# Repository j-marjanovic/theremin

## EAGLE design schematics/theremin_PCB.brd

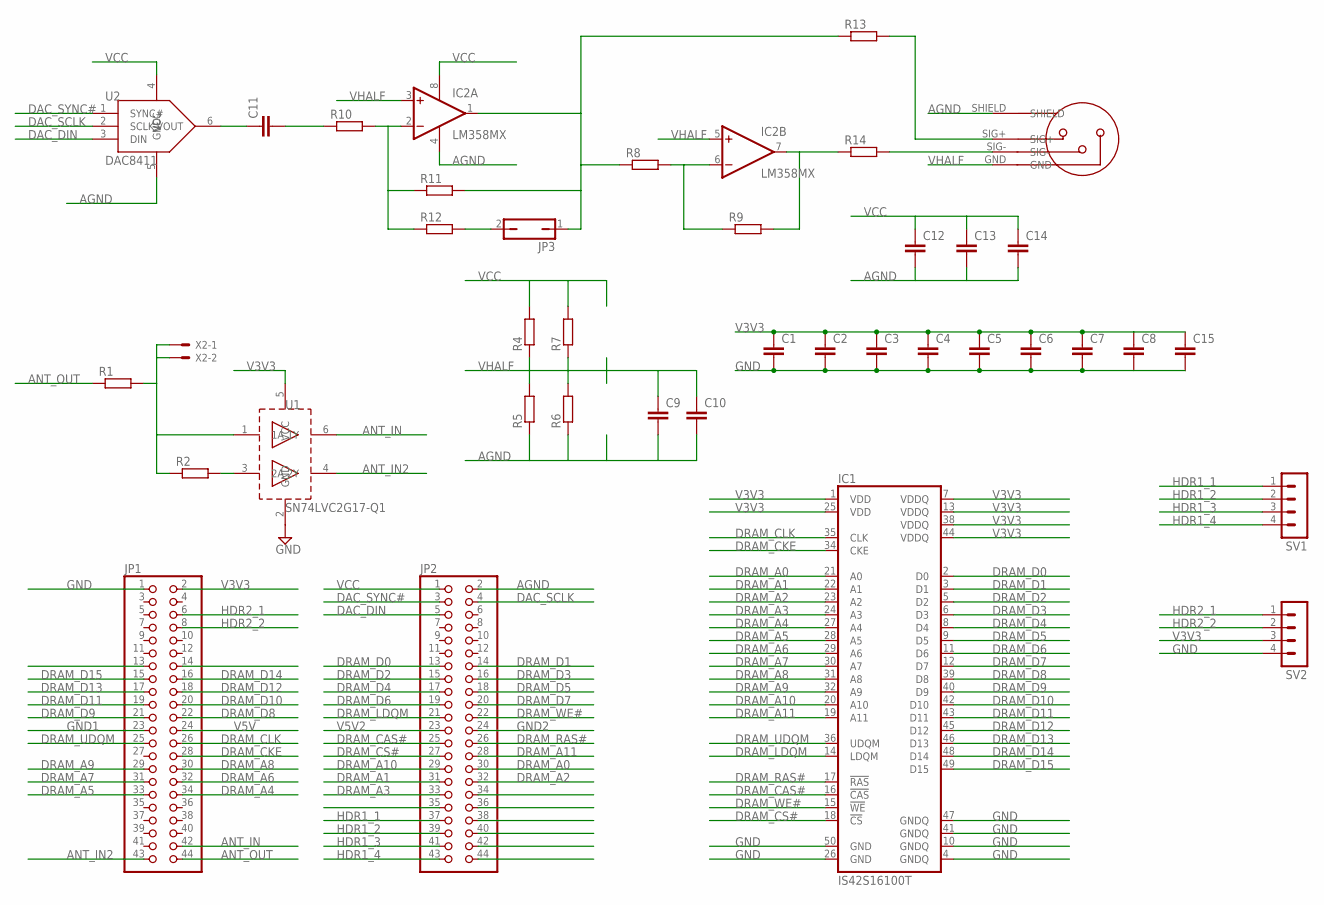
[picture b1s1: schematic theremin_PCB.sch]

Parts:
C1, C2, C3, C4, C5, C6, C7, C8, C9, C10, C11, C12, C13, C14, C15: C-EUC0805; C0805
IC1: IS42S16100T; TSOP50-II
IC2: LM358MX; SO08
JP1, JP2: PINHD-2X22; 2X22
JP3: JP1Q; JP1
R1, R2: R-EU_R0603; R0603
R4, R5, R6, R7, R8, R9, R10, R11, R12, R13, R14: R-EU_M0805; M0805
SV1, SV2: MA04-1
U1: SN74LVC2G17-Q1; DCK_R-PDSO-G6
U2: DAC8411; DCK_R-PDSO-G6
U$1: MINIXLR; MINXLR
X2: KK-156-2

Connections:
AGND: C9.2, C10.2, C12.2, C13.2, C14.2, IC2.4 (V-), JP2.2, R5.1, R6.1, U2.5 (GND), U$1.SHIELD
ANT_IN: JP1.42, U1.6 (1Y)
ANT_IN2: JP1.43, U1.4 (2Y)
ANT_OUT: JP1.44, R1.1
DAC_DIN: JP2.5, U2.3 (DIN)
DAC_SCLK: JP2.4, U2.2 (SCLK)
DAC_SYNC#: JP2.3, U2.1 (SYNC#)
DRAM_A0: IC1.21 (A0), JP2.30
DRAM_A1: IC1.22 (A1), JP2.31
DRAM_A2: IC1.23 (A2), JP2.32
DRAM_A3: IC1.24 (A3), JP2.33
DRAM_A4: IC1.27 (A4), JP1.34
DRAM_A5: IC1.28 (A5), JP1.33
DRAM_A6: IC1.29 (A6), JP1.32
DRAM_A7: IC1.30 (A7), JP1.31
DRAM_A8: IC1.31 (A8), JP1.30
DRAM_A9: IC1.32 (A9), JP1.29
DRAM_A10: IC1.20 (A10), JP2.29
DRAM_A11: IC1.19 (A11), JP2.28
DRAM_CAS#: IC1.16 (!CAS), JP2.25
DRAM_CKE: IC1.34 (CKE), JP1.28
DRAM_CLK: IC1.35 (CLK), JP1.26
DRAM_CS#: IC1.18 (!CS), JP2.27
DRAM_D0: IC1.2 (D0), JP2.13
DRAM_D1: IC1.3 (D1), JP2.14
DRAM_D2: IC1.5 (D2), JP2.15
DRAM_D3: IC1.6 (D3), JP2.16
DRAM_D4: IC1.8 (D4), JP2.17
DRAM_D5: IC1.9 (D5), JP2.18
DRAM_D6: IC1.11 (D6), JP2.19
DRAM_D7: IC1.12 (D7), JP2.20
DRAM_D8: IC1.39 (D8), JP1.22
DRAM_D9: IC1.40 (D9), JP1.21
DRAM_D10: IC1.42 (D10), JP1.20
DRAM_D11: IC1.43 (D11), JP1.19
DRAM_D12: IC1.45 (D12), JP1.18
DRAM_D13: IC1.46 (D13), JP1.17
DRAM_D14: IC1.48 (D14), JP1.16
DRAM_D15: IC1.49 (D15), JP1.15
DRAM_LDQM: IC1.14 (LDQM), JP2.21
DRAM_RAS#: IC1.17 (!RAS), JP2.26
DRAM_UDQM: IC1.36 (UDQM), JP1.25
DRAM_WE#: IC1.15 (!WE), JP2.22
GND: C1.2, C2.2, C3.2, C4.2, C5.2, C6.2, C7.2, C8.2, C15.2, IC1.4 (GNDQ), IC1.10 (GNDQ), IC1.26 (GND), IC1.41 (GNDQ), IC1.47 (GNDQ), IC1.50 (GND), JP1.1, SV2.4, U1.2 (GND)
GND1: JP1.23
GND2: JP2.24
HDR1_1: JP2.37, SV1.1
HDR1_2: JP2.39, SV1.2
HDR1_3: JP2.41, SV1.3
HDR1_4: JP2.43, SV1.4
HDR2_1: JP1.6, SV2.1
HDR2_2: JP1.8, SV2.2
unnamed: R1.2, R2.1, U1.1 (1A), X2.1, X2.2
unnamed: C11.1, U2.6 (VOUT)
unnamed: C11.2, R10.1
unnamed: R2.2, U1.3 (2A)
unnamed: IC2.2 (-IN), R10.2, R11.1, R12.1
unnamed: JP3.2, R12.2
unnamed: IC2.1 (OUT), JP3.1, R8.1, R11.2, R13.1
unnamed: R14.2, U$1.SIG-
unnamed: IC2.6 (-IN), R8.2, R9.1
unnamed: IC2.7 (OUT), R9.2, R14.1
unnamed: R13.2, U$1.SIG+
V3V3: C1.1, C2.1, C3.1, C4.1, C5.1, C6.1, C7.1, C8.1, C15.1, IC1.1 (VDD), IC1.7 (VDDQ), IC1.13 (VDDQ), IC1.25 (VDD), IC1.38 (VDDQ), IC1.44 (VDDQ), JP1.2, SV2.3, U1.5 (VCC)
V5V: JP1.24
V5V2: JP2.23
VCC: C12.1, C13.1, C14.1, IC2.8 (V+), JP2.1, R4.2, R7.2, U2.4 (VCC)
VHALF: C9.1, C10.1, IC2.3 (+IN), IC2.5 (+IN), R4.1, R5.2, R6.2, R7.1, U$1.GND

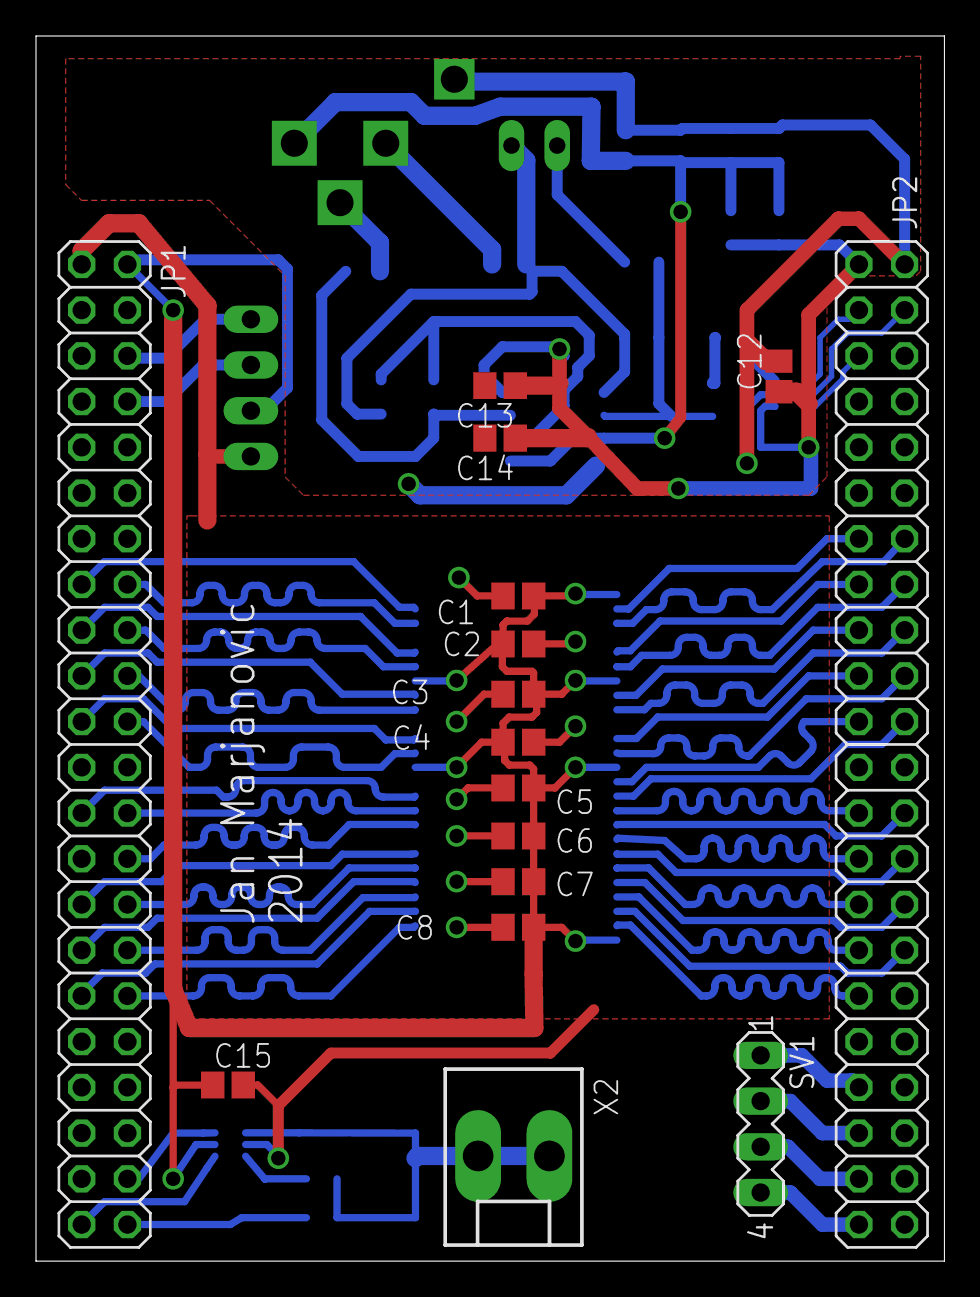
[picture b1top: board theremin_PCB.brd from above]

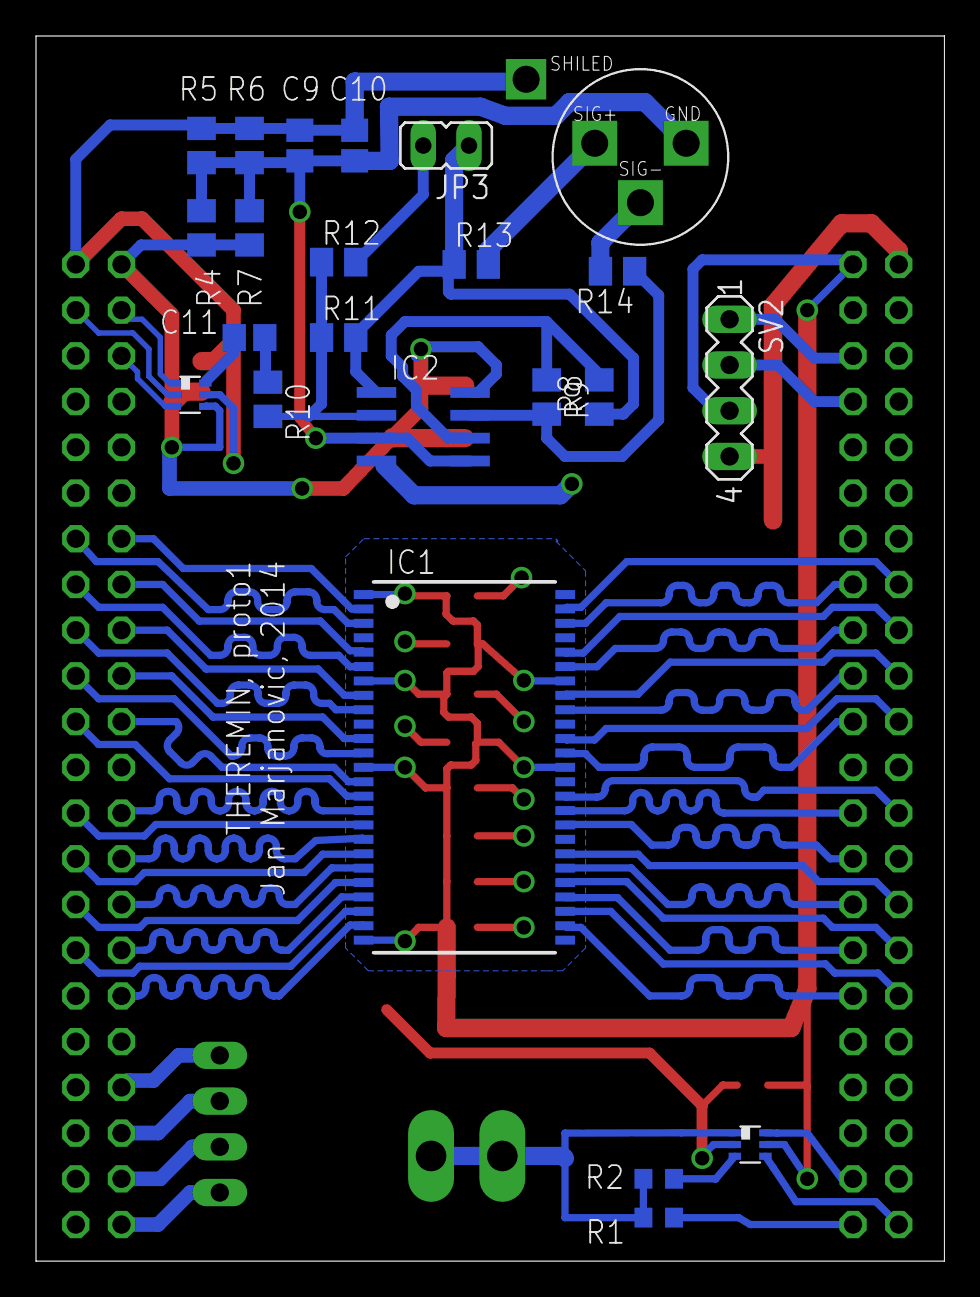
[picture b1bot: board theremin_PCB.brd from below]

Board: 2 copper layers, 50.5 x 68.1 mm, 39 parts (23 on the bottom side), 64 nets.

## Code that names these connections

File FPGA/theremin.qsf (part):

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set_global_assignment -name POWER_BOARD_THERMAL_MODEL "NONE (CONSERVATIVE)"
set_global_assignment -name STRATIX_DEVICE_IO_STANDARD "2.5 V"
set_location_assignment PIN_23 -to CLK_50
set_location_assignment PIN_120 -to ANT_IN
set_location_assignment PIN_124 -to ANT_OUT
set_location_assignment PIN_55 -to DAC_SYNC_n
set_location_assignment PIN_58 -to DAC_SCLK
set_location_assignment PIN_53 -to DAC_DATAI
set_location_assignment PIN_125 -to EXT_RESET_n
set_global_assignment -name ENABLE_SIGNALTAP ON
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set_location_assignment PIN_143 -to DRAM_ADDR[1]
set_location_assignment PIN_2 -to DRAM_ADDR[0]
set_location_assignment PIN_10 -to DRAM_CASn
set_location_assignment PIN_99 -to DRAM_CKE
set_location_assignment PIN_87 -to DRAM_CLK
set_location_assignment PIN_3 -to DRAM_CSn
set_location_assignment PIN_74 -to DRAM_DATA[15]
set_location_assignment PIN_75 -to DRAM_DATA[14]
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set_location_assignment PIN_38 -to DRAM_DATA[2]
set_location_assignment PIN_43 -to DRAM_DATA[1]
set_location_assignment PIN_42 -to DRAM_DATA[0]
set_location_assignment PIN_28 -to DRAM_LDQM
set_location_assignment PIN_11 -to DRAM_RASn
set_location_assignment PIN_86 -to DRAM_UDQM
set_location_assignment PIN_30 -to DRAM_WEn
set_global_assignment -name ENABLE_CONFIGURATION_PINS OFF
set_global_assignment -name ENABLE_BOOT_SEL_PIN OFF
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set_global_assignment -name SLD_NODE_PARAMETER_ASSIGNMENT "SLD_ADVANCED_TRIGGER_ENTITY=basic,1," -section_id auto_signaltap_0
set_global_assignment -name SLD_NODE_PARAMETER_ASSIGNMENT "SLD_TRIGGER_LEVEL_PIPELINE=1" -section_id auto_signaltap_0
set_global_assignment -name SLD_NODE_PARAMETER_ASSIGNMENT "SLD_ENABLE_ADVANCED_TRIGGER=0" -section_id auto_signaltap_0
set_location_assignment PIN_121 -to ANT_IN2
set_global_assignment -name SYSTEMVERILOG_FILE src/filter_50.sv
set_global_assignment -name QIP_FILE mem_controller/synthesis/mem_controller.qip
set_global_assignment -name VERILOG_FILE src/a_ctrls/uart_rx.v
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
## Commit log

2014-09-07 Top level partialy finished
2014-09-07 Skeleton for delay module
2014-09-08 Non-tested version of delay
2014-09-08 Added delay to top module
2014-09-09 Added a_ctrls module and AD5660_SPI module with TB
2014-09-10 Implemented tone gen
2014-09-10 Added constraints file
2014-09-14 Added freq compressor
2014-09-14 UART and ADC bringup
2014-09-14 - Moved UART to system.c - Added createMeasString function
2014-09-14 - Moved ADC part to system.c - Added doMeas function to measure ADCs
2014-09-25 Added schematics
2014-09-25 Added compontents values
2014-09-27 DAC tested
2014-09-27 Added log file from PIC
2014-09-28 Moved a_ctrls module to separate dir
2014-09-28 UART core from OpenCores UART to Bus
2014-09-28 Written and tested a_ctrls
2014-09-28 Tested tone generator
2014-10-04 Connected pots to tone gen to test it
2014-10-08 Memory works
2014-10-09 Extensive test of memory, some minor problems
2014-10-11 Delay module 2 avalon bus interface, preparation for testing
2014-10-11 Delay module 2 avalon bus interface, tested
2014-10-11 Implemeted delay
2014-10-11 Changed maximum possible value for delay
2014-10-23 Filter works, code generation from python not yet
2014-10-23 Cleaned up the code
2014-10-23 Prepared template
2014-10-26 Filter generation works
2014-10-26 Added delay to step, to better show response for high-pass filters
2014-10-31 Measurements with new antenna
2014-10-31 Added averaging filter
2014-10-31 Added logarithm for better response
2014-11-03 Improved logarithm module
2014-11-03 Disabled brown-out reset
2014-11-08 Tested pots for tone gen
2014-11-08 Changed pots mapping
2014-11-08 Delay works OK
2014-11-11 Added volume mixer
2014-11-13 Added LEDs logic

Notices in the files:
FPGA/theremin.qsf:
Copyright (C) 1991-2014 Altera Corporation. All rights reserved.
